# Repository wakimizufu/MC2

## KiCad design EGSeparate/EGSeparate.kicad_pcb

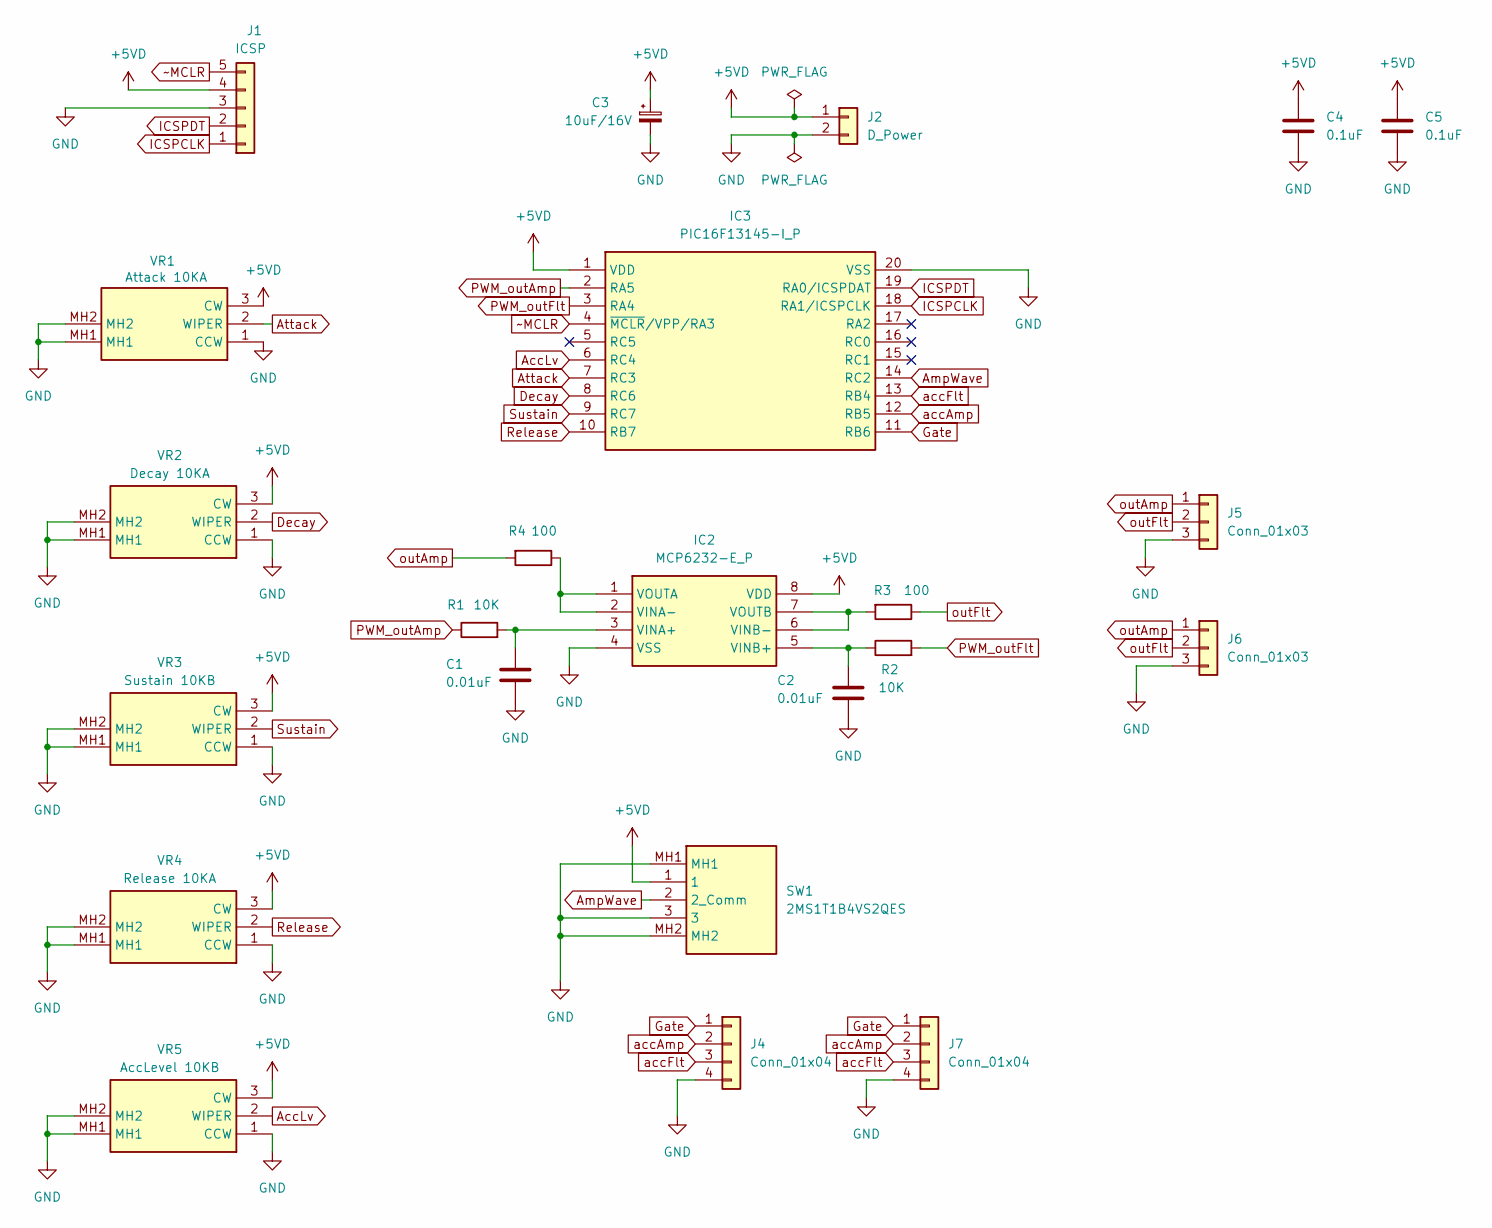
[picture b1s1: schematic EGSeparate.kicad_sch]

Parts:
C1, C2: 0.01uF; C_Disc_D3.4mm_W2.1mm_P2.50mm
C3: 10uF/16V; CP_Radial_D5.0mm_P2.50mm
C4, C5: 0.1uF; C_0805_2012Metric_Pad1.18x1.45mm_HandSolder
IC2: MCP6232-E_P; DIP781W56P254L950H533Q8N; Manufacturer_Part_Number MCP6232-E/P; Mouser Part Number 579-MCP6232-E/P
IC3: PIC16F13145-I_P; DIP794W56P254L2591H533Q20N; Manufacturer_Part_Number PIC16F13145-I/P; Mouser Part Number 579-PIC16F13145-I/P
J1: ICSP; PinHeader_1x05_P2.54mm_Horizontal
J2: D_Power; PinSocket_1x02_P2.54mm_Vertical
J4, J7: Conn_01x04; PinHeader_1x04_P2.54mm_Vertical
J5: Conn_01x03; PinHeader_1x03_P2.54mm_Vertical
J6: Conn_01x03; PinSocket_1x03_P2.54mm_Vertical
R1, R2: 10K; R_Axial_DIN0204_L3.6mm_D1.6mm_P2.54mm_Vertical
R3, R4: 100; R_Axial_DIN0204_L3.6mm_D1.6mm_P2.54mm_Vertical
SW1: 2MS1T1B4VS2QES; Manufacturer_Part_Number 2MS1T1B4VS2QES; Mouser Part Number N/A
VR1: Attack 10KA; RK09D117000B; Manufacturer_Part_Number RK09D117000B; Mouser Part Number 688-RK09D117000B
VR2: Decay 10KA; RK09D117000B; Manufacturer_Part_Number RK09D117000B; Mouser Part Number 688-RK09D117000B
VR3: Sustain 10KB; RK09D117000B; Manufacturer_Part_Number RK09D117000B; Mouser Part Number 688-RK09D117000B
VR4: Release 10KA; RK09D117000B; Manufacturer_Part_Number RK09D117000B; Mouser Part Number 688-RK09D117000B
VR5: AccLevel 10KB; RK09D117000B; Manufacturer_Part_Number RK09D117000B; Mouser Part Number 688-RK09D117000B

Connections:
+5VD: C3.1, C4.1, C5.1, IC2.8 (VDD), IC3.1 (VDD), J1.4, J2.1, SW1.1, VR1.3 (CW), VR2.3 (CW), VR3.3 (CW), VR4.3 (CW), VR5.3 (CW); also elsewhere on the board
AccLv: IC3.6 (RC4), VR5.2 (WIPER)
AmpWave: IC3.14 (RC2), SW1.2 (2_Comm)
Attack: IC3.7 (RC3), VR1.2 (WIPER)
Decay: IC3.8 (RC6), VR2.2 (WIPER)
GND: C1.2, C2.2, C3.2, C4.2, C5.2, IC2.4 (VSS), IC3.20 (VSS), J1.3, J2.2, J4.4, J5.3, J6.3, J7.4, SW1.3, SW1.MH1, SW1.MH2, VR1.1 (CCW), VR1.MH1, VR1.MH2, VR2.1 (CCW), VR2.MH1, VR2.MH2, VR3.1 (CCW), VR3.MH1, VR3.MH2, VR4.1 (CCW), VR4.MH1, VR4.MH2, VR5.1 (CCW), VR5.MH1, VR5.MH2; also elsewhere on the board
Gate: IC3.11 (RB6), J4.1, J7.1
ICSPCLK: IC3.18 (RA1/ICSPCLK), J1.1
ICSPDT: IC3.19 (RA0/ICSPDAT), J1.2
unnamed: C1.1, IC2.3 (VINA+), R1.2
unnamed: IC2.1 (VOUTA), IC2.2 (VINA-), R4.1
unnamed: C2.1, IC2.5 (VINB+), R2.1
unnamed: IC2.6 (VINB-), IC2.7 (VOUTB), R3.2
PWM_outAmp: IC3.2 (RA5), IC3.15 (RC1), R1.1
PWM_outFlt: IC3.3 (RA4), R2.2
Release: IC3.10 (RB7), VR4.2 (WIPER)
Sustain: IC3.9 (RC7), VR3.2 (WIPER)
accAmp: IC3.12 (RB5), J4.2, J7.2
accFlt: IC3.13 (RB4), J4.3, J7.3
outAmp: J5.1, J6.1, R4.2
outFlt: J5.2, J6.2, R3.1
~MCLR: IC3.4 (~MCLR/VPP/RA3), J1.5; also elsewhere on the board

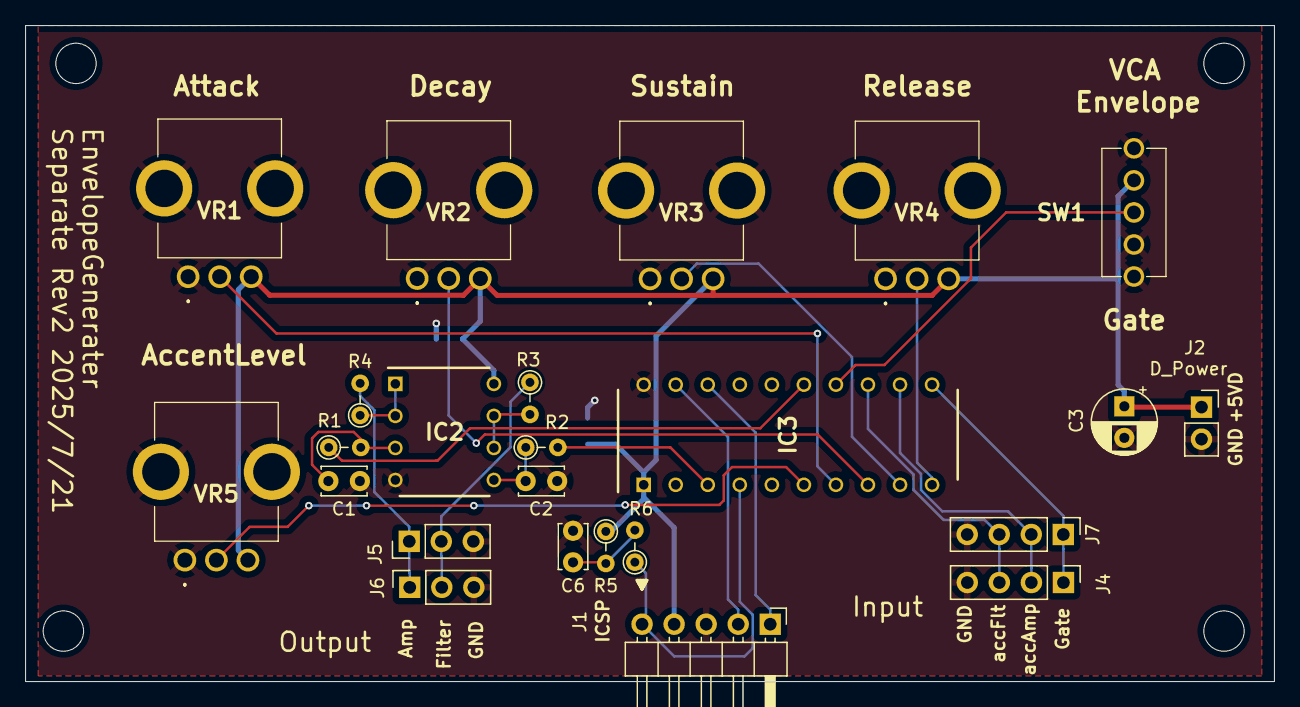
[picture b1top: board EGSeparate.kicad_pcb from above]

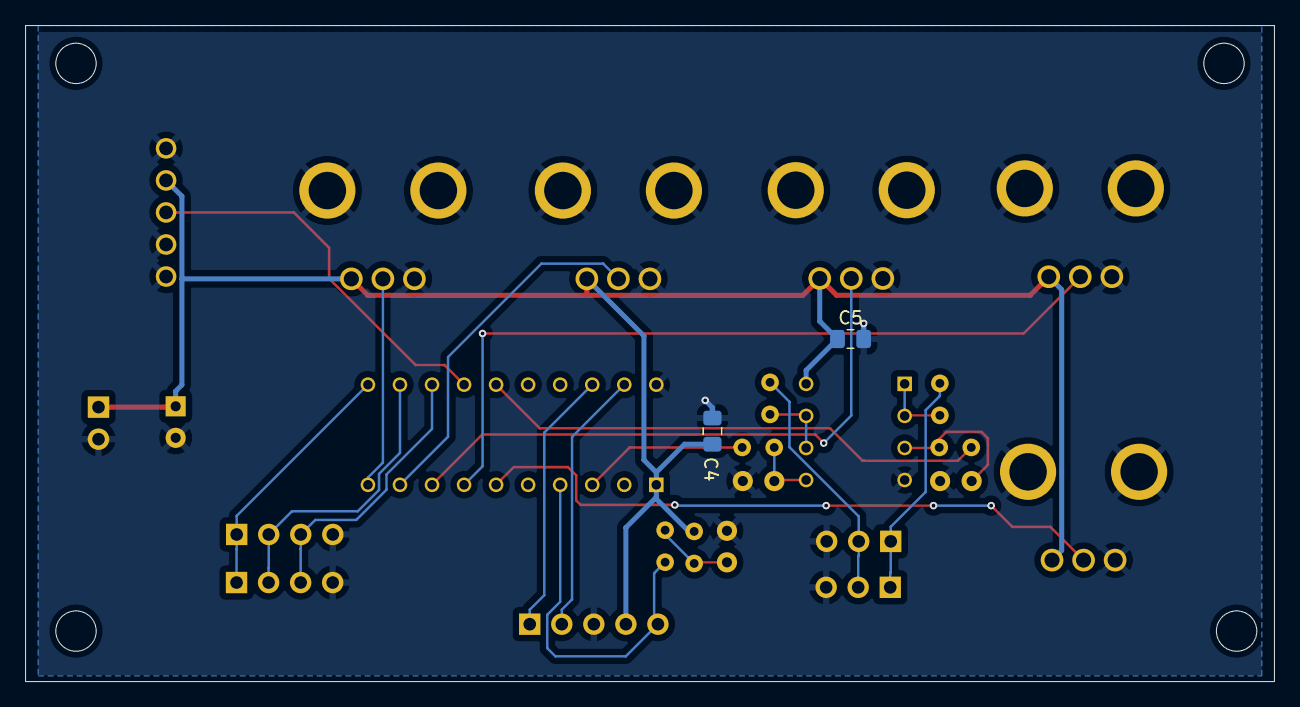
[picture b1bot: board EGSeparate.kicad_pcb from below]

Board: 2 copper layers, 99.0 x 52.0 mm, 26 parts (2 on the bottom side), 23 nets.

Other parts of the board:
C6: 0.01uF; C_Disc_D3.4mm_W2.1mm_P2.50mm
R5: 1K; R_Axial_DIN0204_L3.6mm_D1.6mm_P2.54mm_Vertical
R6: 100; R_Axial_DIN0204_L3.6mm_D1.6mm_P2.54mm_Vertical

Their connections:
+5VD: R5.1; also elsewhere on the board
GND: C6.2; also elsewhere on the board
unnamed: C6.1, R5.2, R6.2
~MCLR: R6.1; also elsewhere on the board

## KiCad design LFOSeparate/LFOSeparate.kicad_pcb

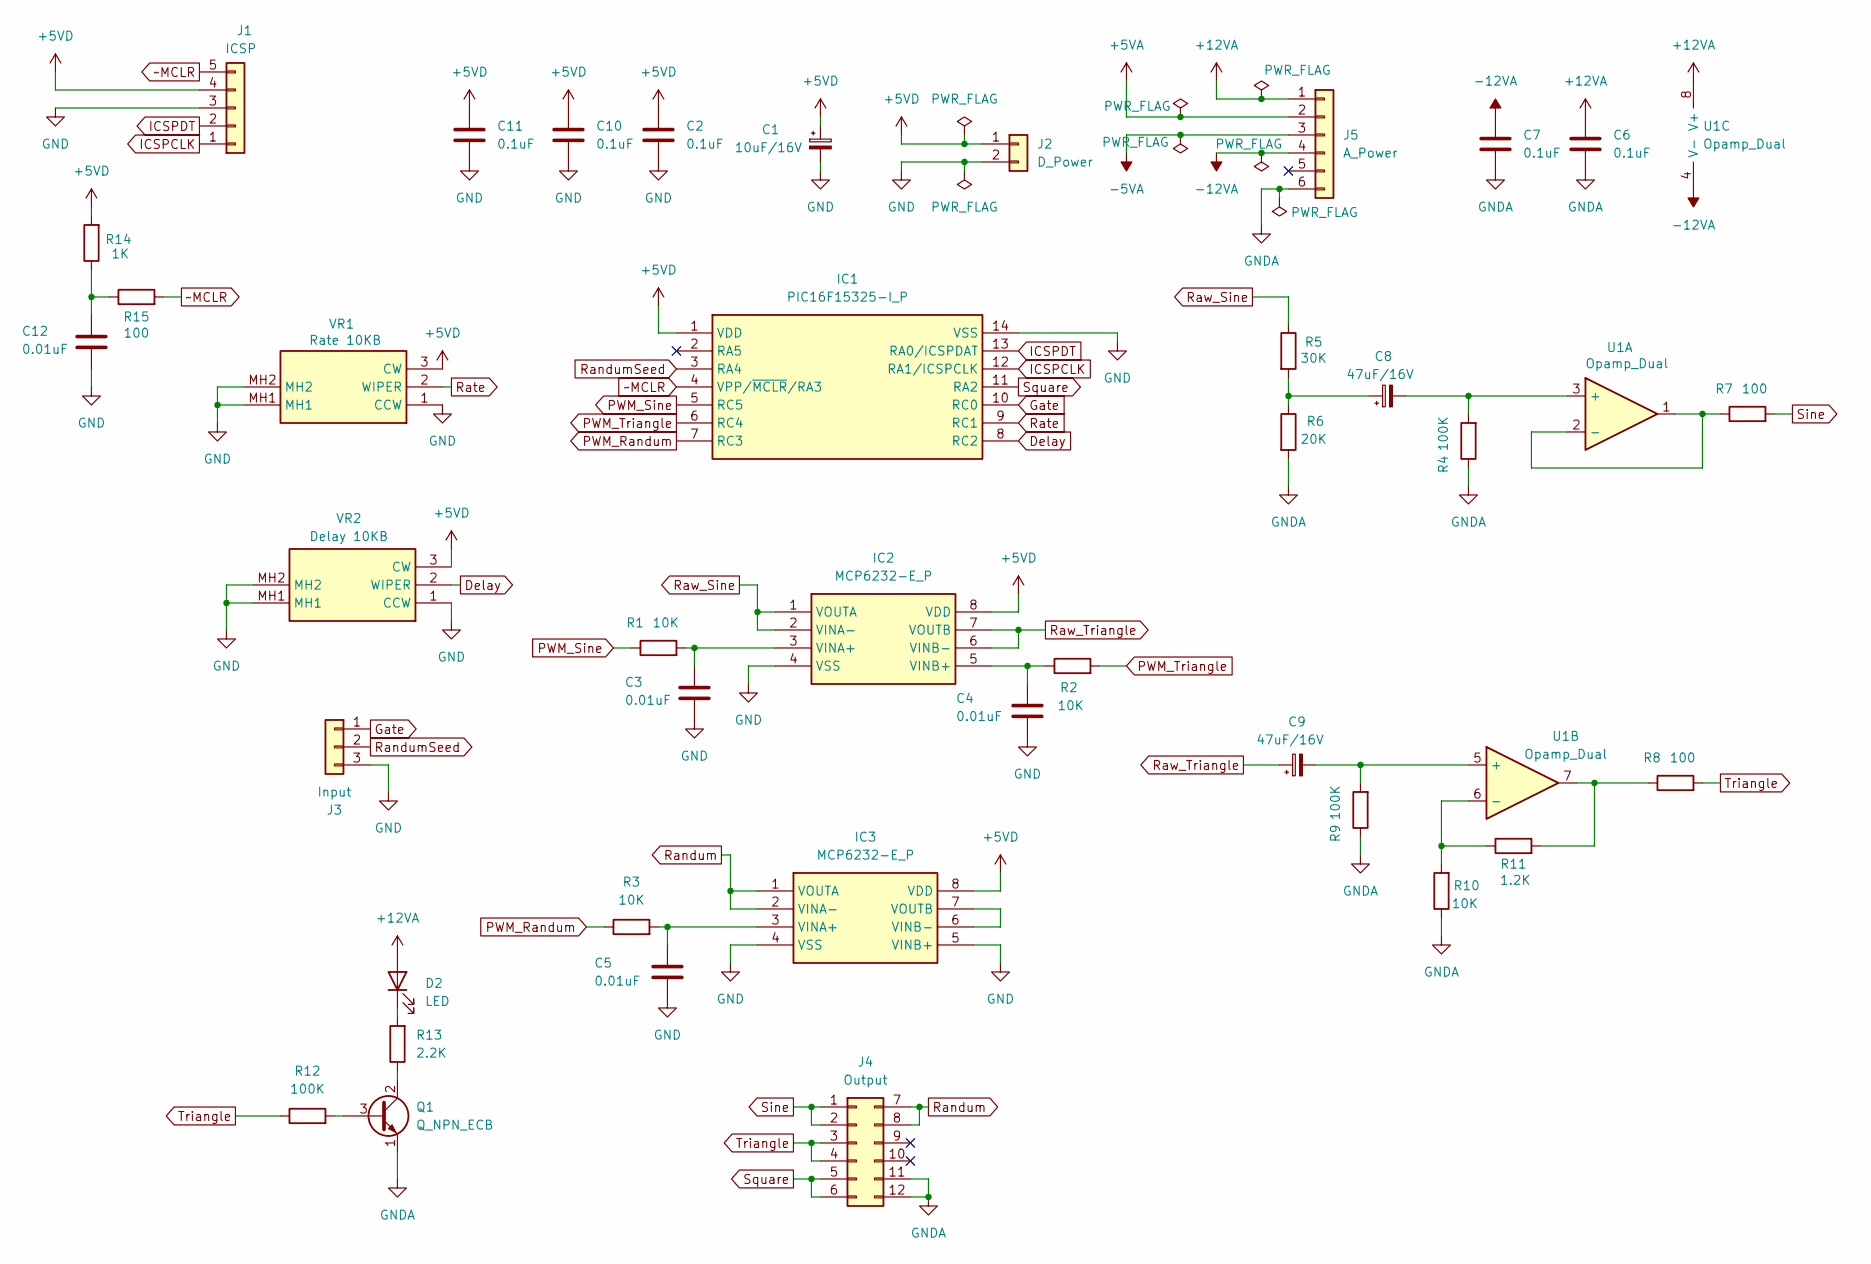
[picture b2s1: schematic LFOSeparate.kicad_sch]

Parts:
C1: 10uF/16V; CP_Radial_D5.0mm_P2.50mm
C2, C6, C7, C10, C11: 0.1uF; C_0805_2012Metric_Pad1.18x1.45mm_HandSolder
C3, C4, C5, C12: 0.01uF; C_Disc_D3.4mm_W2.1mm_P2.50mm
C8, C9: 47uF/16V; CP_Radial_D5.0mm_P2.50mm
D2: LED; LED_D5.0mm_FlatTop
IC1: PIC16F15325-I_P; DIP-14_W7.62mm_LongPads; Manufacturer_Part_Number PIC16F15325-I/P; Mouser Part Number 579-PIC16F15325-I/P
IC2, IC3: MCP6232-E_P; DIP-8_W7.62mm_LongPads; Manufacturer_Part_Number MCP6232-E/P; Mouser Part Number 579-MCP6232-E/P
J1: ICSP; PinHeader_1x05_P2.54mm_Horizontal
J2: D_Power; PinSocket_1x02_P2.54mm_Vertical
J3: Input; PinSocket_1x03_P2.54mm_Vertical
J4: Output; PinSocket_2x06_P2.54mm_Vertical
J5: A_Power; PinHeader_1x06_P2.54mm_Vertical
Q1: Q_NPN_ECB; TO-92_HandSolder
R1, R2, R3, R10: 10K; R_Axial_DIN0204_L3.6mm_D1.6mm_P2.54mm_Vertical
R4, R9, R12: 100K; R_Axial_DIN0204_L3.6mm_D1.6mm_P2.54mm_Vertical
R5: 30K; R_Axial_DIN0204_L3.6mm_D1.6mm_P2.54mm_Vertical
R6: 20K; R_Axial_DIN0204_L3.6mm_D1.6mm_P2.54mm_Vertical
R7, R8, R15: 100; R_Axial_DIN0204_L3.6mm_D1.6mm_P2.54mm_Vertical
R11: 1.2K; R_Axial_DIN0204_L3.6mm_D1.6mm_P2.54mm_Vertical
R13: 2.2K; R_Axial_DIN0204_L3.6mm_D1.6mm_P2.54mm_Vertical
R14: 1K; R_Axial_DIN0204_L3.6mm_D1.6mm_P2.54mm_Vertical
U1: Opamp_Dual; DIP-8_W7.62mm_LongPads
VR1: Rate 10KB; RK09D117000B; Manufacturer_Part_Number RK09D117000B; Mouser Part Number 688-RK09D117000B
VR2: Delay 10KB; RK09D117000B; Manufacturer_Part_Number RK09D117000B; Mouser Part Number 688-RK09D117000B

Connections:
+5VA: J5.2
+5VD: C1.1, C2.1, C10.1, C11.1, IC1.1 (VDD), IC2.8 (VDD), IC3.8 (VDD), J1.4, J2.1, R14.2, VR1.3 (CW), VR2.3 (CW)
+12VA: C6.1, D2.2 (A), J5.1, U1.8 (V+)
-5VA: J5.3
-12VA: C7.1, J5.4, U1.4 (V-)
Delay: IC1.8 (RC2), VR2.2 (WIPER)
GND: C1.2, C2.2, C3.2, C4.2, C5.2, C10.2, C11.2, C12.2, IC1.14 (VSS), IC2.4 (VSS), IC3.4 (VSS), IC3.5 (VINB+), J1.3, J2.2, J3.3, VR1.1 (CCW), VR1.MH1, VR1.MH2, VR2.1 (CCW), VR2.MH1, VR2.MH2
GNDA: C6.2, C7.2, J4.11, J4.12, J5.6, Q1.1 (E), R4.1, R6.2, R9.1, R10.1
Gate: IC1.10 (RC0), J3.1
ICSPCLK: IC1.12 (RA1/ICSPCLK), J1.1
ICSPDT: IC1.13 (RA0/ICSPDAT), J1.2
unnamed: C8.1, R5.2, R6.1
unnamed: C12.1, R14.1, R15.1
unnamed: D2.1 (K), R13.2
unnamed: C3.1, IC2.3 (VINA+), R1.2
unnamed: C4.1, IC2.5 (VINB+), R2.1
unnamed: C5.1, IC3.3 (VINA+), R3.2
unnamed: IC3.6 (VINB-), IC3.7 (VOUTB)
unnamed: Q1.3 (B), R12.2
unnamed: Q1.2 (C), R13.1
unnamed: R8.1, R11.2, U1.7
unnamed: C8.2, R4.2, U1.3 (+)
unnamed: R7.1, U1.1, U1.2 (-)
unnamed: C9.2, R9.2, U1.5 (+)
unnamed: R10.2, R11.1, U1.6 (-)
PWM_Randum: IC1.7 (RC3), R3.1
PWM_Sine: IC1.5 (RC5), R1.1
PWM_Triangle: IC1.6 (RC4), R2.2
Randum: IC3.1 (VOUTA), IC3.2 (VINA-), J4.7, J4.8
RandumSeed: IC1.3 (RA4), J3.2
Rate: IC1.9 (RC1), VR1.2 (WIPER)
Raw_Sine: IC2.1 (VOUTA), IC2.2 (VINA-), R5.1
Raw_Triangle: C9.1, IC2.6 (VINB-), IC2.7 (VOUTB)
Sine: J4.1, J4.2, R7.2
Square: IC1.11 (RA2), J4.5, J4.6
Triangle: J4.3, J4.4, R8.2, R12.1
~MCLR: IC1.4 (VPP/~MCLR/RA3), J1.5, R15.2

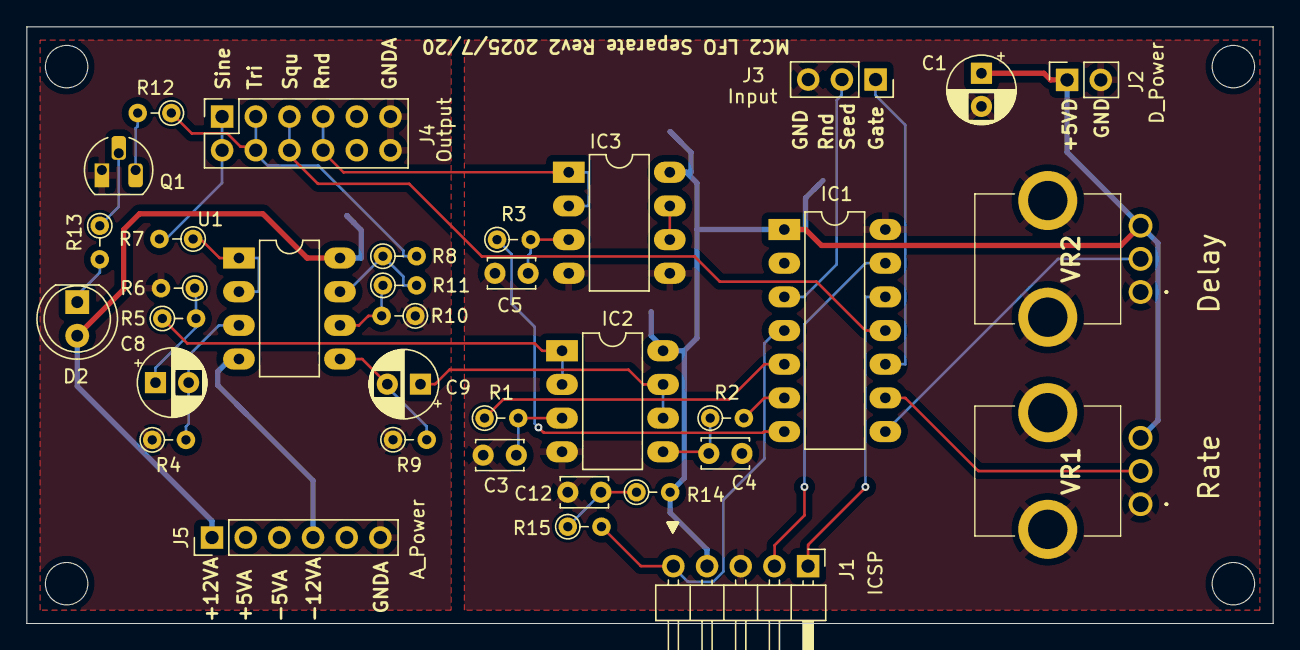
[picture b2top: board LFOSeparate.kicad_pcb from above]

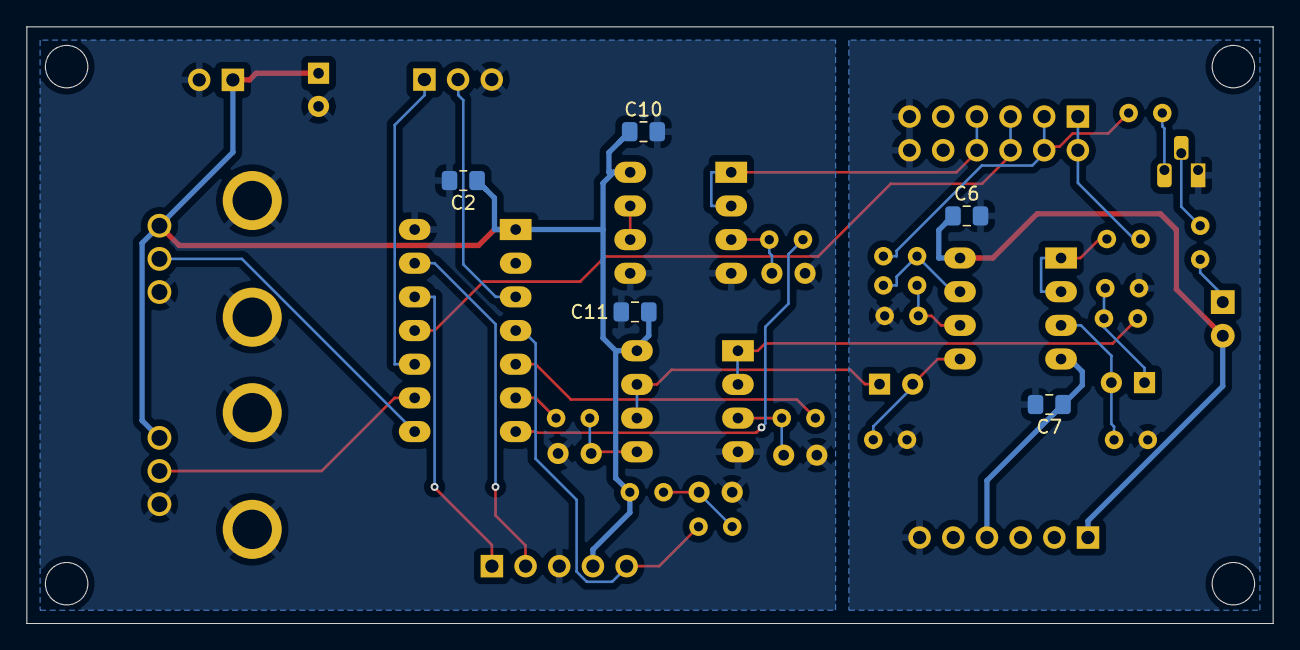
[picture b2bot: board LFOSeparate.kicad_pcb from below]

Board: 2 copper layers, 94.0 x 45.0 mm, 40 parts (5 on the bottom side), 35 nets.

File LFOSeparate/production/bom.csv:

Designator,Footprint,Quantity,Value,LCSC Part #
C1,CP_Radial_D5.0mm_P2.50mm,1,10uF/16V,
"C10, C11, C2, C6, C7",0805,5,0.1uF,
"C3, C4, C5",C_Disc_D3.4mm_W2.1mm_P2.50mm,3,0.01uF,
"C8, C9",CP_Radial_D5.0mm_P2.50mm,2,1uF/16V,
D1,D_DO-34_SOD68_P2.54mm_Vertical_AnodeUp,1,D,
D2,LED_D5.0mm_FlatTop,1,LED,
IC1,DIP-14_W7.62mm_LongPads,1,PIC16F15325-I_P,
"IC2, IC3",DIP-8_W7.62mm_LongPads,2,MCP6232-E_P,
J1,PinHeader_1x05_P2.54mm_Horizontal,1,ICSP,
J2,PinSocket_1x02_P2.54mm_Vertical,1,D_Power,
J3,PinSocket_1x03_P2.54mm_Vertical,1,Input,
J4,PinSocket_2x06_P2.54mm_Vertical,1,Output,
J5,PinHeader_1x06_P2.54mm_Vertical,1,A_Power,
Q1,TO-92_HandSolder,1,Q_NPN_ECB,
"R1, R10, R2, R3, R5",R_Axial_DIN0204_L3.6mm_D1.6mm_P2.54mm_Vertical,5,10K,
R11,R_Axial_DIN0204_L3.6mm_D1.6mm_P2.54mm_Vertical,1,12K,
"R12, R4, R9",R_Axial_DIN0204_L3.6mm_D1.6mm_P2.54mm_Vertical,3,100K,
R13,R_Axial_DIN0204_L3.6mm_D1.6mm_P2.54mm_Vertical,1,1K,
R6,R_Axial_DIN0204_L3.6mm_D1.6mm_P2.54mm_Vertical,1,3.9K,
"R7, R8",R_Axial_DIN0204_L3.6mm_D1.6mm_P2.54mm_Vertical,2,100,
U1,DIP-8_W7.62mm_LongPads,1,Opamp_Dual,
VR1,RK09D117000B,1,Rate 10KB,
VR2,RK09D117000B,1,Delay 10KB,

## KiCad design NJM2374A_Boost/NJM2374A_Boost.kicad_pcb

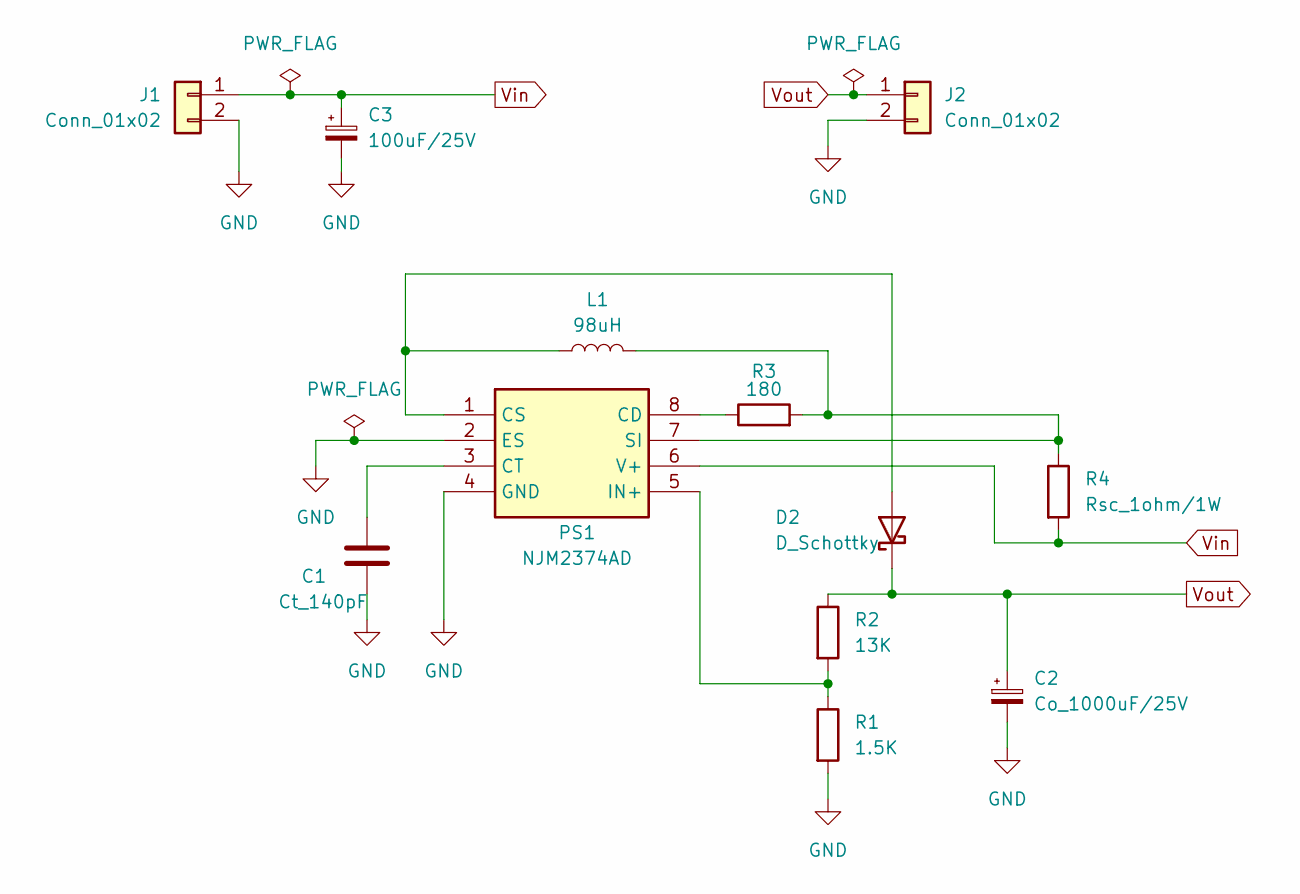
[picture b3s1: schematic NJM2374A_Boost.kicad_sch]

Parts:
C1: Ct_140pF; C_Disc_D7.5mm_W2.5mm_P5.00mm
C2: Co_1000uF/25V; CP_Radial_D5.0mm_P2.50mm
C3: 100uF/25V; CP_Radial_D5.0mm_P2.50mm
D2: D_Schottky; D_DO-41_SOD81_P7.62mm_Horizontal
J1, J2: Conn_01x02; PinHeader_1x02_P2.54mm_Vertical
L1: 98uH; L_Radial_D9.5mm_P5.00mm_Fastron_07HVP
PS1: NJM2374AD; DIP-8_W7.62mm_LongPads; Manufacturer_Part_Number NJM2374AD; Mouser Part Number 513-NJM2374AD
R1: 1.5K; R_Axial_DIN0207_L6.3mm_D2.5mm_P10.16mm_Horizontal
R2: 13K; R_Axial_DIN0207_L6.3mm_D2.5mm_P10.16mm_Horizontal
R3: 180; R_Axial_DIN0207_L6.3mm_D2.5mm_P10.16mm_Horizontal
R4: Rsc_1ohm/1W; R_Axial_DIN0309_L9.0mm_D3.2mm_P12.70mm_Horizontal

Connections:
GND: C1.1, C2.2, C3.2, J1.2, J2.2, PS1.2 (ES), PS1.4 (GND), R1.2
unnamed: D2.2 (A), L1.1, PS1.1 (CS)
unnamed: PS1.8 (CD), R3.1
unnamed: C1.2, PS1.3 (CT)
unnamed: PS1.5 (IN+), R1.1, R2.2
unnamed: L1.2, PS1.7 (SI), R3.2, R4.1
Vin: C3.1, J1.1, PS1.6 (V+), R4.2
Vout: C2.1, D2.1 (K), J2.1, R2.1

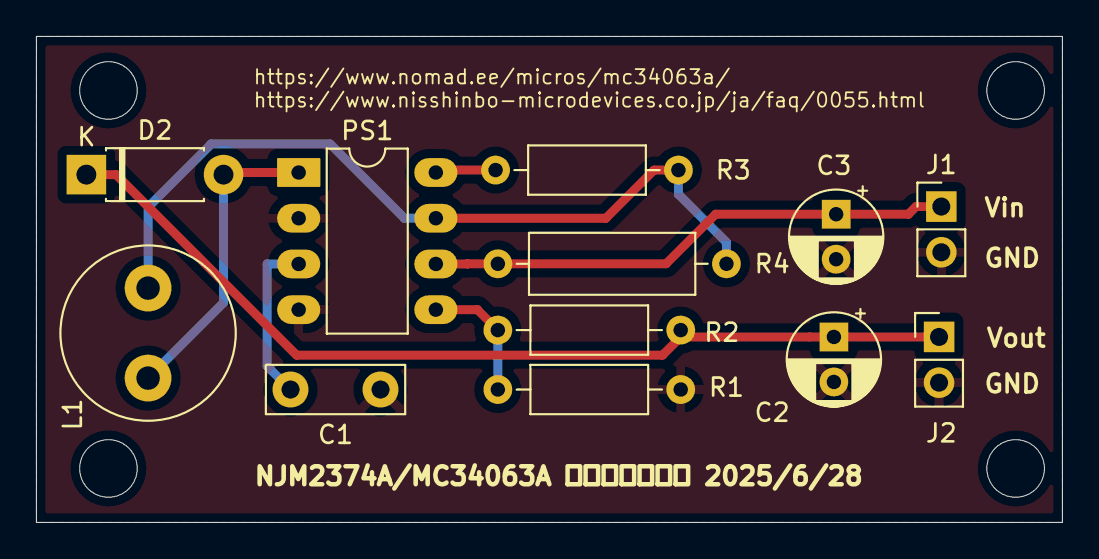
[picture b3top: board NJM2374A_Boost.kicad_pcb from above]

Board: 2 copper layers, 57.0 x 27.0 mm, 12 parts (0 on the bottom side), 8 nets.

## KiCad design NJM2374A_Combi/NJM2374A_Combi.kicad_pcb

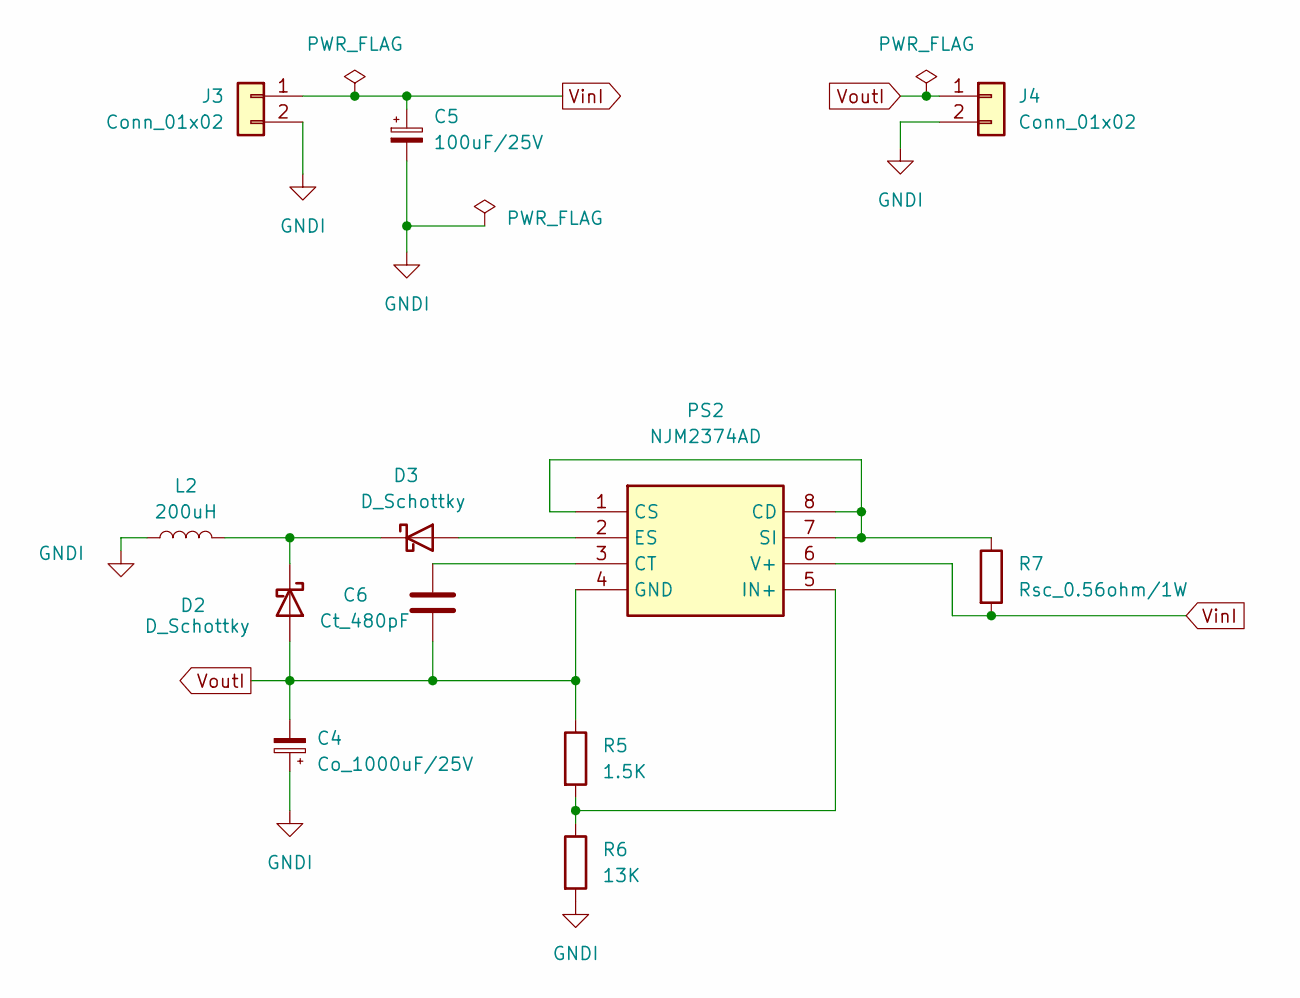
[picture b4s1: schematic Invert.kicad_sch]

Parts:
C4: Co_1000uF/25V; CP_Radial_D5.0mm_P2.50mm
C5: 100uF/25V; CP_Radial_D5.0mm_P2.50mm
C6: Ct_480pF; C_Disc_D7.5mm_W2.5mm_P5.00mm
D2, D3: D_Schottky; D_DO-41_SOD81_P7.62mm_Horizontal
J3, J4: Conn_01x02; PinHeader_1x02_P2.54mm_Vertical
L2: 200uH; L_Radial_D9.5mm_P5.00mm_Fastron_07HVP
PS2: NJM2374AD; DIP762W56P254L880H425Q8N; Manufacturer_Part_Number NJM2374AD; Mouser Part Number 513-NJM2374AD
R5: 1.5K; R_Axial_DIN0207_L6.3mm_D2.5mm_P10.16mm_Horizontal
R6: 13K; R_Axial_DIN0207_L6.3mm_D2.5mm_P10.16mm_Horizontal
R7: Rsc_0.56ohm/1W; R_Axial_DIN0309_L9.0mm_D3.2mm_P12.70mm_Horizontal

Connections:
GNDI: C4.1, C5.2, J3.2, J4.2, L2.1, R6.2
unnamed: D2.1 (K), D3.1 (K), L2.2
unnamed: D3.2 (A), PS2.2 (ES)
unnamed: PS2.1 (CS), PS2.7 (SI), PS2.8 (CD), R7.1
unnamed: C6.2, PS2.3 (CT)
unnamed: PS2.5 (IN+), R5.2, R6.1
VinI: C5.1, J3.1, PS2.6 (V+), R7.2
VoutI: C4.2, C6.1, D2.2 (A), J4.1, PS2.4 (GND), R5.1

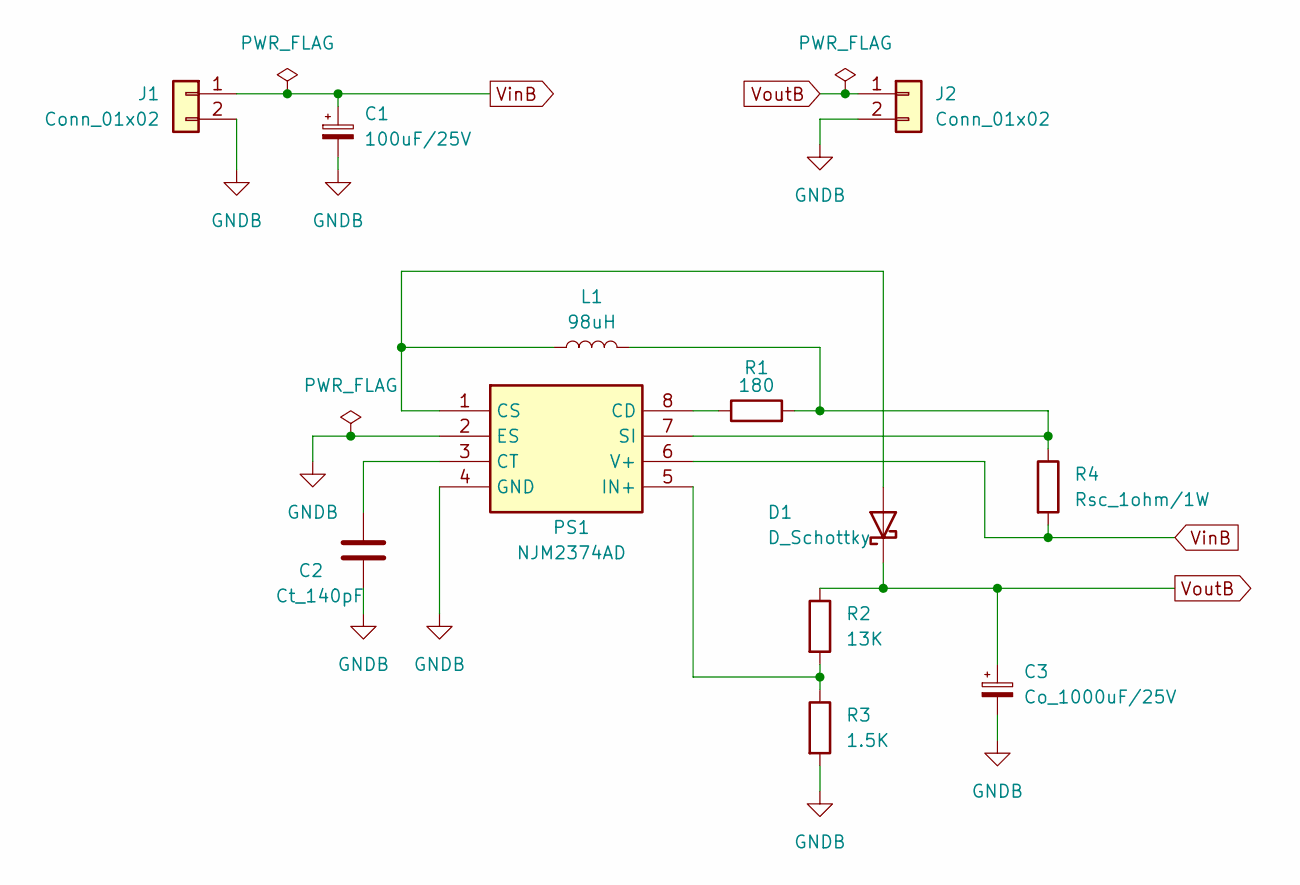
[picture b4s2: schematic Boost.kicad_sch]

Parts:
C1: 100uF/25V; CP_Radial_D5.0mm_P2.50mm
C2: Ct_140pF; C_Disc_D7.5mm_W2.5mm_P5.00mm
C3: Co_1000uF/25V; CP_Radial_D5.0mm_P2.50mm
D1: D_Schottky; D_DO-41_SOD81_P7.62mm_Horizontal
J1, J2: Conn_01x02; PinHeader_1x02_P2.54mm_Vertical
L1: 98uH; L_Radial_D9.5mm_P5.00mm_Fastron_07HVP
PS1: NJM2374AD; DIP-8_W7.62mm_LongPads; Manufacturer_Part_Number NJM2374AD; Mouser Part Number 513-NJM2374AD
R1: 180; R_Axial_DIN0207_L6.3mm_D2.5mm_P10.16mm_Horizontal
R2: 13K; R_Axial_DIN0207_L6.3mm_D2.5mm_P10.16mm_Horizontal
R3: 1.5K; R_Axial_DIN0207_L6.3mm_D2.5mm_P10.16mm_Horizontal
R4: Rsc_1ohm/1W; R_Axial_DIN0309_L9.0mm_D3.2mm_P12.70mm_Horizontal

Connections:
GNDB: C1.2, C2.1, C3.2, J1.2, J2.2, PS1.2 (ES), PS1.4 (GND), R3.2
unnamed: D1.2 (A), L1.1, PS1.1 (CS)
unnamed: PS1.8 (CD), R1.1
unnamed: C2.2, PS1.3 (CT)
unnamed: PS1.5 (IN+), R2.2, R3.1
unnamed: L1.2, PS1.7 (SI), R1.2, R4.1
VinB: C1.1, J1.1, PS1.6 (V+), R4.2
VoutB: C3.1, D1.1 (K), J2.1, R2.1

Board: 2 copper layers, 24 parts (0 on the bottom side), 16 nets, no tracks yet.

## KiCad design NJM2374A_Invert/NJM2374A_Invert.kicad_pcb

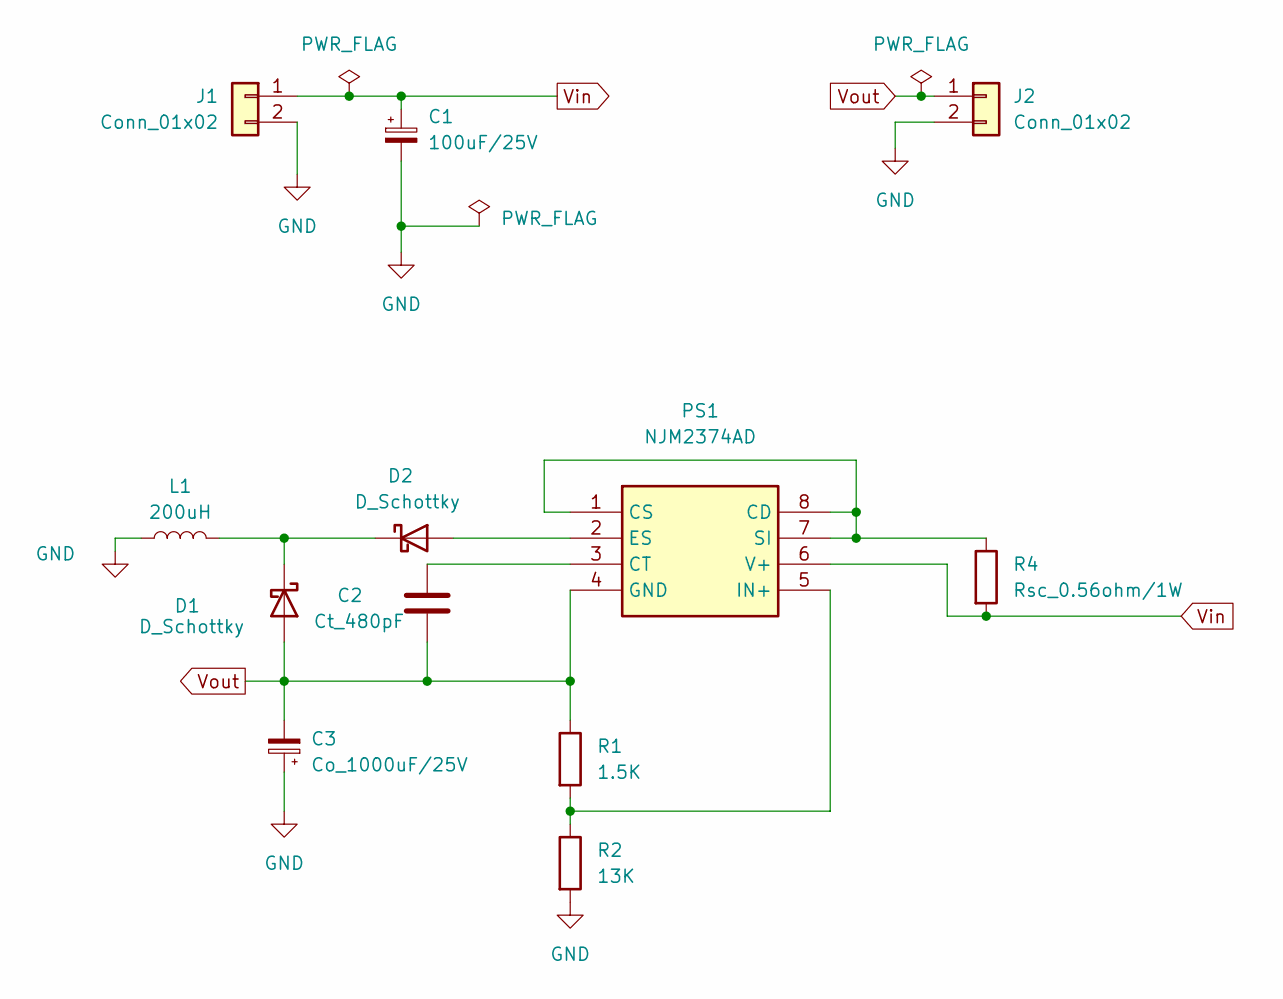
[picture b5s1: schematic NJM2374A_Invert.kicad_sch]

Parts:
C1: 100uF/25V; CP_Radial_D5.0mm_P2.50mm
C2: Ct_480pF; C_Disc_D7.5mm_W2.5mm_P5.00mm
C3: Co_1000uF/25V; CP_Radial_D5.0mm_P2.50mm
D1, D2: D_Schottky; D_DO-41_SOD81_P7.62mm_Horizontal
J1, J2: Conn_01x02; PinHeader_1x02_P2.54mm_Vertical
L1: 200uH; L_Radial_D9.5mm_P5.00mm_Fastron_07HVP
PS1: NJM2374AD; DIP762W56P254L880H425Q8N; Manufacturer_Part_Number NJM2374AD; Mouser Part Number 513-NJM2374AD
R1: 1.5K; R_Axial_DIN0207_L6.3mm_D2.5mm_P10.16mm_Horizontal
R2: 13K; R_Axial_DIN0207_L6.3mm_D2.5mm_P10.16mm_Horizontal
R4: Rsc_0.56ohm/1W; R_Axial_DIN0309_L9.0mm_D3.2mm_P12.70mm_Horizontal

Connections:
GND: C1.2, C3.1, J1.2, J2.2, L1.1, R2.2
unnamed: D1.1 (K), D2.1 (K), L1.2
unnamed: D2.2 (A), PS1.2 (ES)
unnamed: PS1.1 (CS), PS1.7 (SI), PS1.8 (CD), R4.1
unnamed: C2.2, PS1.3 (CT)
unnamed: PS1.5 (IN+), R1.2, R2.1
Vin: C1.1, J1.1, PS1.6 (V+), R4.2
Vout: C2.1, C3.2, D1.2 (A), J2.1, PS1.4 (GND), R1.1

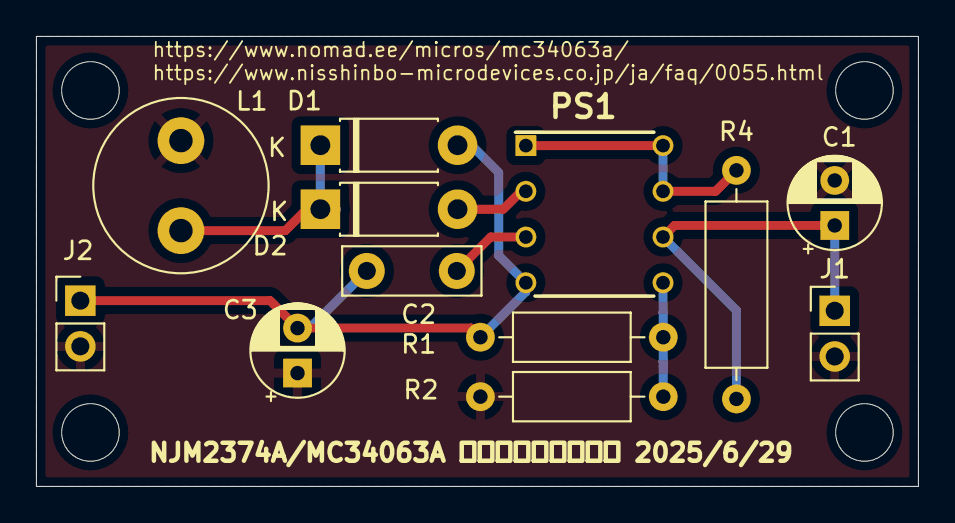
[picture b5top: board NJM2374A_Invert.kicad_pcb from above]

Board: 2 copper layers, 49.0 x 25.0 mm, 12 parts (0 on the bottom side), 8 nets.
